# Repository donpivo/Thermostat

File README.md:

Description:
https://retronics.no/2023/11/08/diy-high-temperature-programmable-thermostat/

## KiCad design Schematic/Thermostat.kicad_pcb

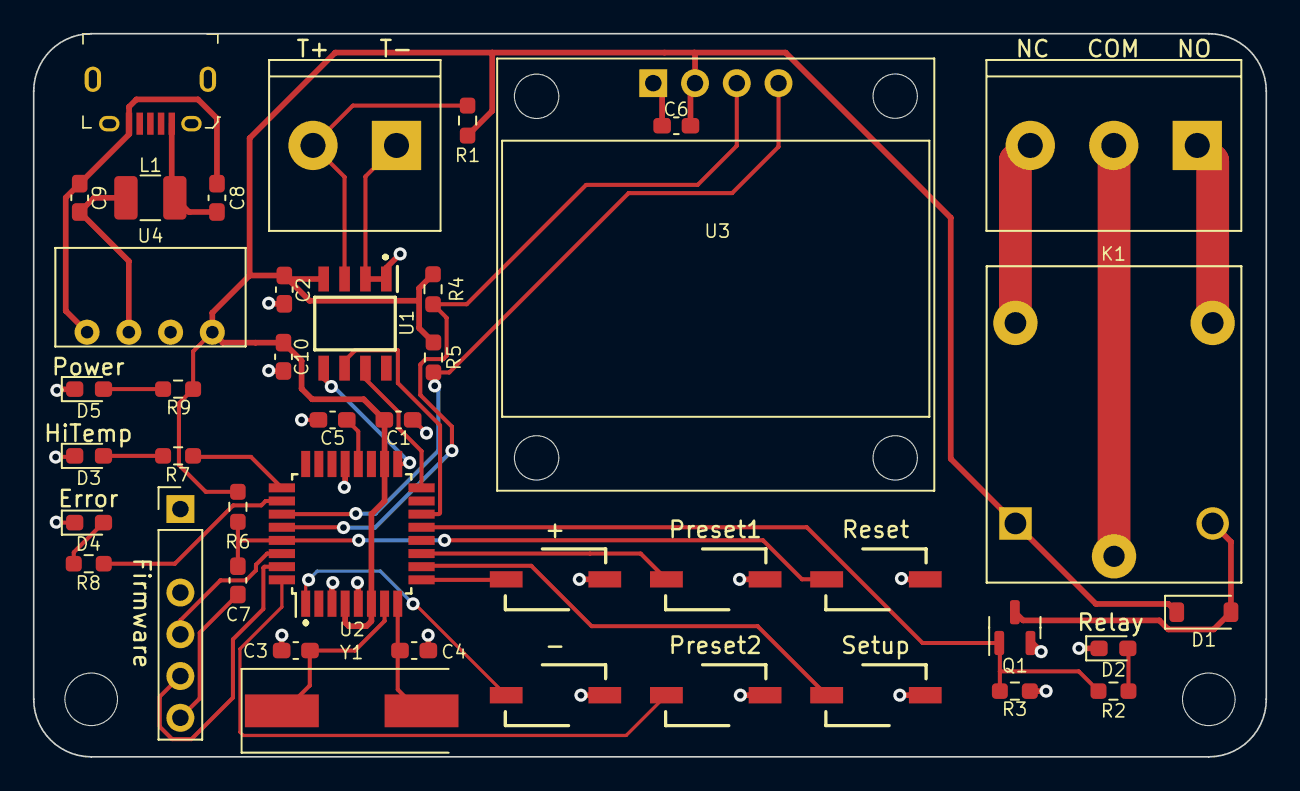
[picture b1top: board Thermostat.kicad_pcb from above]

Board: 2 copper layers, 75.0 x 44.0 mm, 44 parts (0 on the bottom side), 34 nets.

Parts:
C1, C2, C5: 100nF; C_0603_1608Metric_Pad1.08x0.95mm_HandSolder
C3, C4: 22pF; C_0603_1608Metric_Pad1.08x0.95mm_HandSolder
C6: 1µF; C_0603_1608Metric_Pad1.08x0.95mm_HandSolder
C7: 10nF; C_0603_1608Metric_Pad1.08x0.95mm_HandSolder
C8, C9: 4.7µF; C_0603_1608Metric_Pad1.08x0.95mm_HandSolder
C10: 10µF; C_0603_1608Metric_Pad1.08x0.95mm_HandSolder
D1: 1N5819W; D_SOD-123
D2: Yellow; LED_0603_1608Metric_Pad1.05x0.95mm_HandSolder
D3: Orange; LED_0603_1608Metric_Pad1.05x0.95mm_HandSolder
D4: Red; LED_0603_1608Metric_Pad1.05x0.95mm_HandSolder
D5: Green; LED_0603_1608Metric_Pad1.05x0.95mm_HandSolder
H1, H2: MountingHole; MountingHole_3.2mm_M3
J1: Relay conn.; ScrewTerminal_DB128L-5.08-3P-BK-S
J2: Thermocouple; ScrewTerminal_DB128L-5.08-2P-BK-S
J3: Firmware; PinHeader_1x06_P2.54mm_Vertical_Minus2
J4: USB_B_Micro; USB_Micro_B_Female_10118194-0001LF
K1: SONGLE_SRD_05VDC_SL_C; RELAY_SRD-05VDC-SL-C
L1: CBC3225T6R8MR; L_1210_3225Metric_Pad1.42x2.65mm_HandSolder
Q1: BSS138; SOT-23
R1: 1MΩ; R_0603_1608Metric_Pad0.98x0.95mm_HandSolder
R2, R7, R8, R9: 1kΩ; R_0603_1608Metric_Pad0.98x0.95mm_HandSolder
R3, R6: 10kΩ; R_0603_1608Metric_Pad0.98x0.95mm_HandSolder
R4, R5: 4.7kΩ; R_0603_1608Metric_Pad0.98x0.95mm_HandSolder
SW1: Temp+; AlpsAlpine_SKQYPCE010
SW2: Preset1; AlpsAlpine_SKQYPCE010
SW3: Reset; AlpsAlpine_SKQYPCE010
SW4: Temp-; AlpsAlpine_SKQYPCE010
SW5: Preset2; AlpsAlpine_SKQYPCE010
SW6: Setup; AlpsAlpine_SKQYPCE010
U1: MAX6675; SOIC127P600X175-8N
U2: ATMEGA328P-AU; TQFP-32_7x7mm_P0.8mm
U3: Display_OLED_0.96_I2C; Display_OLED_0.96in_I2C
U4: B0505S-1WR3; B0505S
Y1: 16MHz; Crystal_SMD_HC49-SD

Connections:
+5V: C1.1, C2.1, C6.1, C10.2, D1.1 (K), K1.A1, R1.1, R4.1, R5.1, R6.1, R9.1, U1.4 (VCC), U2.4 (VCC), U2.6 (VCC), U2.18 (AVCC), U3.2 (VCC), U4.4 (VOUT)
Earth: C8.1, C9.1, J4.5 (GND), U4.1 (GND)
GND: C1.2, C2.2, C3.2, C4.2, C5.1, C6.2, C10.1, D2.1 (K), D3.1 (K), D4.1 (K), D5.1 (K), J2.1, J3.1, Q1.2 (S), R3.2, SW1.2, SW2.2, SW3.2, SW4.2, SW5.2, SW6.2, U1.1 (GND), U1.2 (T-), U2.3 (GND), U2.5 (GND), U2.21 (GND), U3.1 (GND), U4.3 (0V)
LED_ERROR: R8.1, U2.26 (A3)
LED_HITEMP: R7.1, U2.25 (A2)
unnamed: D1.2 (A), K1.A2, Q1.3 (D)
unnamed: D2.2 (A), R2.2
unnamed: D3.2 (A), R7.2
unnamed: D4.2 (A), R8.2
unnamed: D5.2 (A), R9.2
unnamed: J1.1, K1.NO
unnamed: J1.2, K1.COM
unnamed: J1.3, K1.NC
unnamed: J2.2, R1.2, U1.3 (T+)
unnamed: J3.4, U2.30 (D0/RX)
unnamed: J3.5, U2.31 (D1/TX)
unnamed: C7.1, J3.6
unnamed: C8.2, J4.1 (VBUS), L1.1
unnamed: C5.2, U2.20 (AREF)
unnamed: C3.1, U2.7 (XTAL1), Y1.1
unnamed: C4.1, U2.8 (XTAL2), Y1.2
unnamed: C9.2, L1.2, U4.2 (VIN)
RLY_CTRL: Q1.1 (G), R2.1, R3.1, U2.13 (D9(PWM))
SCL: R4.2, U2.28 (A5/SCL), U3.3 (SCL)
SDA: R5.2, U2.27 (A4/SDA), U3.4 (SDA)
SPI_CS: U1.6 (~CS), U2.14 (D10(PWM)/SS)
SPI_MISO: U1.7 (SO), U2.16 (D12/MISO)
SPI_SCK: U1.5 (SCK), U2.17 (D13/SCK)
SW_Preset1: SW2.1, U2.11 (D7)
SW_Preset2: SW5.1, U2.32 (D2/INT0)
SW_Reset: C7.2, R6.2, SW3.1, U2.29 (~RESET)
SW_Setup: SW6.1, U2.10 (D6(PWM))
SW_Temp+: SW1.1, U2.9 (D5(PWM))
SW_Temp-: SW4.1, U2.1 (D3(PWM)/INT1)

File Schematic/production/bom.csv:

Designator,Footprint,Quantity,Value,LCSC Part #
"C1, C2, C5",0603,3,100nF,
C10,0603,1,10µF,
"C3, C4",0603,2,22pF,
C6,0603,1,1µF,
C7,0603,1,10nF,
"C8, C9",0603,2,4.7µF,
D1,D_SOD-123,1,1N5819W,
D2,0603,1,Yellow,
D3,0603,1,Orange,
D4,0603,1,Red,
D5,0603,1,Green,
"H1, H2",MountingHole_3.2mm_M3,2,MountingHole,
J1,ScrewTerminal_DB128L-5.08-3P-BK-S,1,Relay conn.,
J2,ScrewTerminal_DB128L-5.08-2P-BK-S,1,Thermocouple,
J3,PinHeader_1x06_P2.54mm_Vertical_Minus2,1,Firmware,
J4,USB_Micro_B_Female_10118194-0001LF,1,USB_B_Micro,
K1,RELAY_SRD-05VDC-SL-C,1,SONGLE_SRD_05VDC_SL_C,
L1,1210,1,CBC3225T6R8MR,
Q1,SOT-23,1,BSS138,
R1,0603,1,1MΩ,
"R2, R7, R8, R9",0603,4,1kΩ,
"R3, R6",0603,2,10kΩ,
"R4, R5",0603,2,4.7kΩ,
SW1,AlpsAlpine_SKQYPCE010,1,Temp+,
SW2,AlpsAlpine_SKQYPCE010,1,Preset1,
SW3,AlpsAlpine_SKQYPCE010,1,Reset,
SW4,AlpsAlpine_SKQYPCE010,1,Temp-,
SW5,AlpsAlpine_SKQYPCE010,1,Preset2,
SW6,AlpsAlpine_SKQYPCE010,1,Setup,
U1,SOIC127P600X175-8N,1,MAX6675,
U2,TQFP-32_7x7mm_P0.8mm,1,ATMEGA328P-AU,
U3,Display_OLED_0.96in_I2C,1,Display_OLED_0.96_I2C,
U4,B0505S,1,B0505S-1WR3,
Y1,Crystal_SMD_HC49-SD,1,16MHz,

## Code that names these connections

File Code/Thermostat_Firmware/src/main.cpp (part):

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#include <max6675.h>
#include <EEPROM.h>
#include <U8glib.h>
#define PIN_RLY_CTRL 9
#define PIN_MAX6675_DO 12
#define PIN_MAX6675_CS 10
#define PIN_MAX6675_CLK 13
#define PIN_SW_TEMP_UP 5
#define PIN_SW_TEMP_DN 3
#define PIN_SW_SETUP 6
#define PIN_SW_PRESET1 7
#define PIN_SW_PRESET2 2
#define PIN_LED_HITEMP A2
#define PIN_LED_ERROR A3
#define MAX_SET_TEMP 1000
#define MIN_SET_TEMP 0
#define DEFAULT_TEMP 50
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
void setup() 
{
  pinMode(PIN_RLY_CTRL, OUTPUT);
  pinMode(PIN_LED_HITEMP, OUTPUT);
  pinMode(PIN_LED_ERROR, OUTPUT);
  pinMode(PIN_SW_TEMP_UP, INPUT_PULLUP);
  pinMode(PIN_SW_TEMP_DN, INPUT_PULLUP);
  pinMode(PIN_SW_SETUP, INPUT_PULLUP);
  pinMode(PIN_SW_PRESET1, INPUT_PULLUP);
  pinMode(PIN_SW_PRESET2, INPUT_PULLUP);
  Serial.begin(115200);
  // clearEEPROM();
  readEEPROM(0);
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      lastMenuItemChange=millis();
    }
  }
  else if((!digitalRead(PIN_SW_SETUP))&&((millis()-lastMenuItemChange)>500))
  {
    if(((selectedMenuItem++)>=3)||((mode!=1) && (selectedMenuItem==3))) 
    {
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    // Serial.println(selectedMenuItem);
    lastMenuItemChange=millis();
  }
  else if(!digitalRead(PIN_SW_PRESET1)&&(preset1counter<100))
  {
    if ((preset1counter++)>8)
    {
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      preset1counter=110;
    }
  }
  else if((digitalRead(PIN_SW_PRESET1))&&(preset1counter>0))
  {
    if(preset1counter>100) preset1counter--;
    else if(preset1counter>10) preset1counter=0;
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      preset1counter=0;
    }
  } 
  else if(!digitalRead(PIN_SW_PRESET2)&&(preset2counter<100))
  {
    if ((preset2counter++)>8)
    {
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      preset2counter=110;
    }
  }
  else if((digitalRead(PIN_SW_PRESET2))&&(preset2counter>0))
  {
    if(preset2counter>100) preset2counter--;
    else if(preset2counter>10) preset2counter=0;
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  lastActualTempRead=millis();
  if(actualTemp<0) 
  {
    digitalWrite(PIN_LED_ERROR, HIGH);
    sensorError=true;
    digitalWrite(PIN_RLY_CTRL, LOW);
    digitalWrite(PIN_LED_HITEMP, LOW);
  }
  else
  {
    actualTemp=((actualTemp+offset)>0)? actualTemp+offset : 0;
    maxTemp=(maxTemp<actualTemp)?actualTemp:maxTemp;
    minTemp=(minTemp>actualTemp)?actualTemp:minTemp;
    digitalWrite(PIN_LED_ERROR, LOW);
    sensorError=false;
    switch (mode)
    {
    case 0:
      digitalWrite(PIN_RLY_CTRL, LOW);
      digitalWrite(PIN_LED_HITEMP, LOW);
      break;
    case 1:
      if(((actualTemp<=setTemp)&&!overtempReached)||(actualTemp<=(setTemp-hysteresis)))
      {
        digitalWrite(PIN_RLY_CTRL, HIGH);
        overtempReached=false;
      }
      else
      {
        digitalWrite(PIN_RLY_CTRL, LOW);
        overtempReached=true;
        digitalWrite(PIN_LED_HITEMP, HIGH);
      }
      digitalWrite(PIN_LED_HITEMP, (actualTemp>setTemp));
      break;
    case 2:
      if((!overtempReached)&&(actualTemp<setTemp))
      {
        digitalWrite(PIN_RLY_CTRL, HIGH);
      }
      else
      {
        overtempReached=true;
        digitalWrite(PIN_RLY_CTRL, LOW);
        digitalWrite(PIN_LED_HITEMP, HIGH);
      }
    default:
      break;
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
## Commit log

2023-09-12 Added status LEDs, changed button functions
2023-10-04 Added pull-up/pull-down resistors for sensor, removed redundant LEDs
2023-10-16 Altered button configuration
2023-10-19 Added status LEDs, rearranged buttons
2023-11-05 Firmware v1.0
2023-11-05 File cleanup
2023-11-08 Shared libs
2023-11-24 Corrected behavior at sensor error
